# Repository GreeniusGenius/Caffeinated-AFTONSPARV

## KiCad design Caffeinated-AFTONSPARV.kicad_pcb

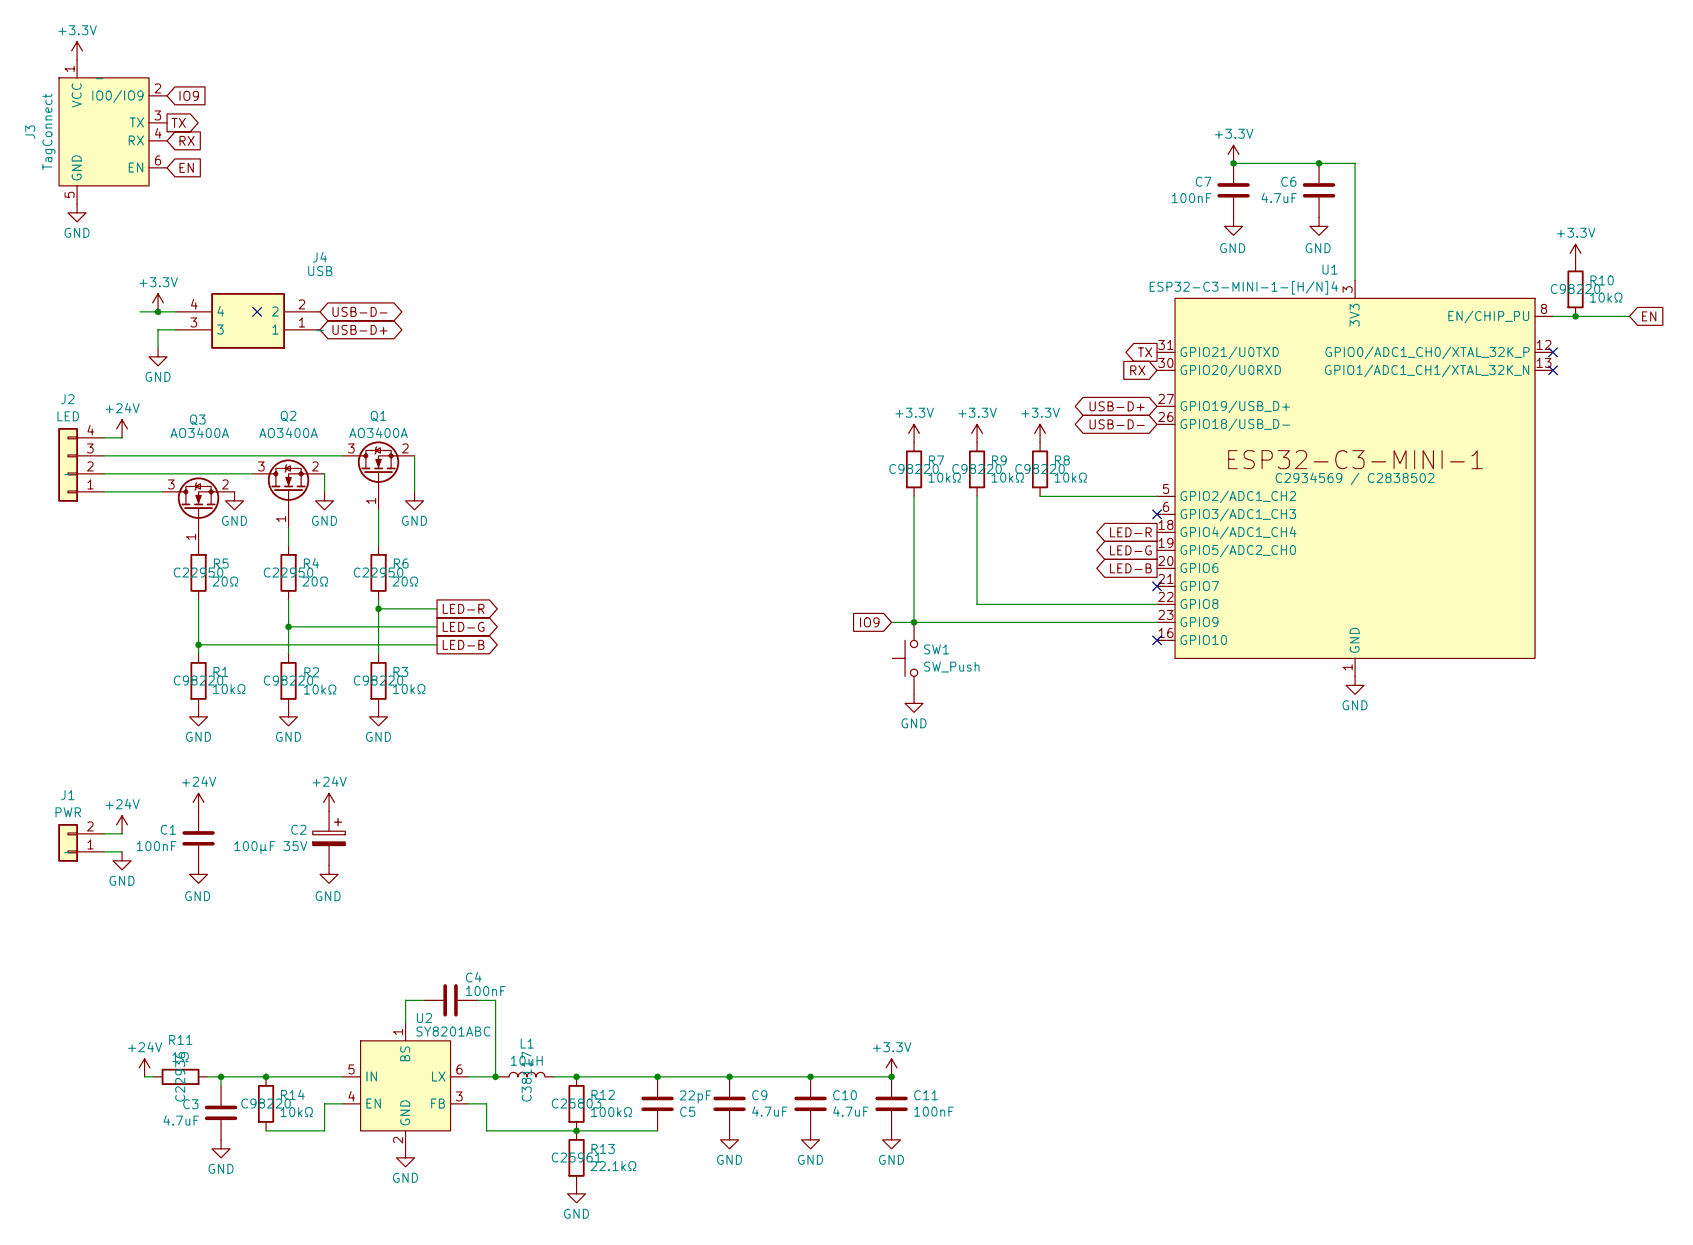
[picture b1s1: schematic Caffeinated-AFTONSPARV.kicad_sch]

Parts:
C1, C4, C7, C11: 100nF; C_0603_1608Metric; LCSC C14663
C2: 100µF 35V; CP_Radial_D6.3mm_P2.50mm; LCSC C2831717
C3, C6, C9, C10: 4.7uF; C_0805_2012Metric; LCSC C560882
C5: 22pF; C_0603_1608Metric; LCSC C105620
J1: PWR; PinSocket_1x02_P2.54mm_Vertical
J2: LED; PinSocket_1x04_P2.54mm_Vertical
J3: TagConnect; Tag-Connect_TC2030-IDC-NL_2x03_P1.27mm_Vertical
J4: USB; BM04B-SRSS-TB_LFSN_; Mouser Part Number N/A
L1: 10uH; L_Sunlord_SWPA4030S; LCSC C38117
Q1, Q2, Q3: AO3400A; SOT-23; LCSC C347475
R1, R2, R3, R7, R8, R9, R10, R14: 10kΩ; R_0603_1608Metric; LCSC C98220
R4, R5, R6: 20Ω; R_0603_1608Metric; LCSC C22950
R11: 1Ω; R_0603_1608Metric; LCSC C22936
R12: 100kΩ; R_0603_1608Metric; LCSC C25803
R13: 22.1kΩ; R_0603_1608Metric; LCSC C25961
SW1: SW_Push; YTS-C005; LCSC C2910748
U1: ESP32-C3-MINI-1-[H/N]4; ESP32-C3-MINI-1; LCSC C2934569 / C2838502
U2: SY8201ABC; SOT-23-6; LCSC C108052

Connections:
+3.3V: C5.2, C6.1, C7.1, C9.1, C10.1, C11.1, J3.1 (VCC), J4.4, L1.2, R7.1, R8.1, R9.1, R10.1, R12.1, U1.3 (3V3)
+24V: C1.1, C2.1, J1.2, J2.4, R11.1
EN: J3.6 (EN), R10.2, U1.8 (EN/CHIP_PU)
GND: C1.2, C2.2, C3.2, C6.2, C7.2, C9.2, C10.2, C11.2, J1.1, J3.5 (GND), J4.3, Q1.2 (S), Q2.2 (S), Q3.2 (S), R1.2, R2.2, R3.2, R13.2, SW1.1, U1.1 (GND), U1.2 (GND), U1.11 (GND), U1.14 (GND), U1.36 (GND), U1.37 (GND), U1.38 (GND), U1.39 (GND), U1.40 (GND), U1.41 (GND), U1.42 (GND), U1.43 (GND), U1.44 (GND), U1.45 (GND), U1.46 (GND), U1.47 (GND), U1.48 (GND), U1.49 (GND), U1.50 (GND), U1.51 (GND), U1.52 (GND), U1.53 (GND), U2.2 (GND)
IO9: J3.2 (IO0/IO9), R7.2, SW1.2, U1.23 (GPIO9)
LED-B: R1.1, R5.1, U1.20 (GPIO6)
LED-G: R2.1, R4.1, U1.19 (GPIO5/ADC2_CH0)
LED-R: R3.1, R6.1, U1.18 (GPIO4/ADC1_CH4)
unnamed: J2.1, Q3.3 (D)
unnamed: J2.2, Q2.3 (D)
unnamed: J2.3, Q1.3 (D)
unnamed: Q1.1 (G), R6.2
unnamed: Q2.1 (G), R4.2
unnamed: Q3.1 (G), R5.2
unnamed: R8.2, U1.5 (GPIO2/ADC1_CH2)
unnamed: R9.2, U1.22 (GPIO8)
unnamed: C4.2, U2.1 (BS)
unnamed: R14.2, U2.4 (EN)
unnamed: C5.1, R12.2, R13.1, U2.3 (FB)
unnamed: C3.1, R11.2, R14.1, U2.5 (IN)
unnamed: C4.1, L1.1, U2.6 (LX)
RX: J3.4 (RX), U1.30 (GPIO20/U0RXD)
TX: J3.3 (TX), U1.31 (GPIO21/U0TXD)
USB-D+: J4.1, U1.27 (GPIO19/USB_D+)
USB-D-: J4.2, U1.26 (GPIO18/USB_D-)

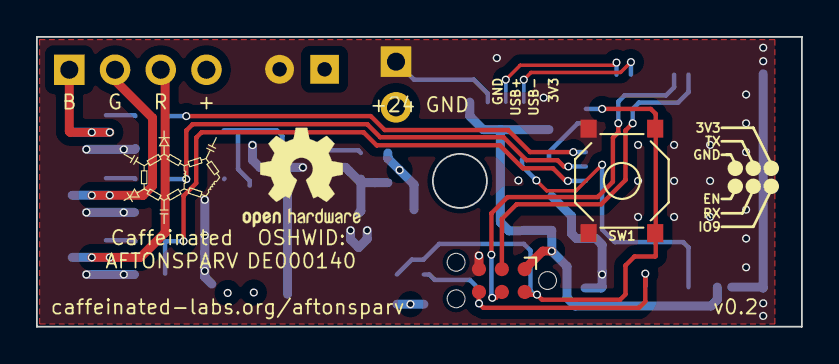
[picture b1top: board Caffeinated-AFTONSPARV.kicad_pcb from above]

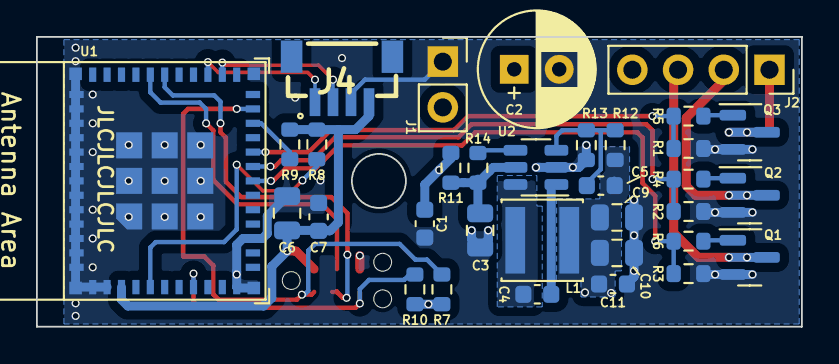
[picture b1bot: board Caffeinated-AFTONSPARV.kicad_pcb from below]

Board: 4 copper layers, 42.5 x 16.1 mm, 35 parts (33 on the bottom side), 25 nets.

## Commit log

2025-05-18 Added JST SH 4P
    Added JST SH 4P connector for UART flashing, to schematic and PCB, and rerouted traces and components to make that happen
